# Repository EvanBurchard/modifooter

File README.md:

# Problem
Modifier keys are hard to reach. And chords involving them are
especially taxing on power users who use them frequently.

# Solution
Put it in your feet.  Like an organist, pianist or a guitarist, you
don't have to be stuck just using your hands.

# TODO:
* Rework the looping structure to use interrupts a la http://www.arduino.cc/en/Reference/AttachInterrupt

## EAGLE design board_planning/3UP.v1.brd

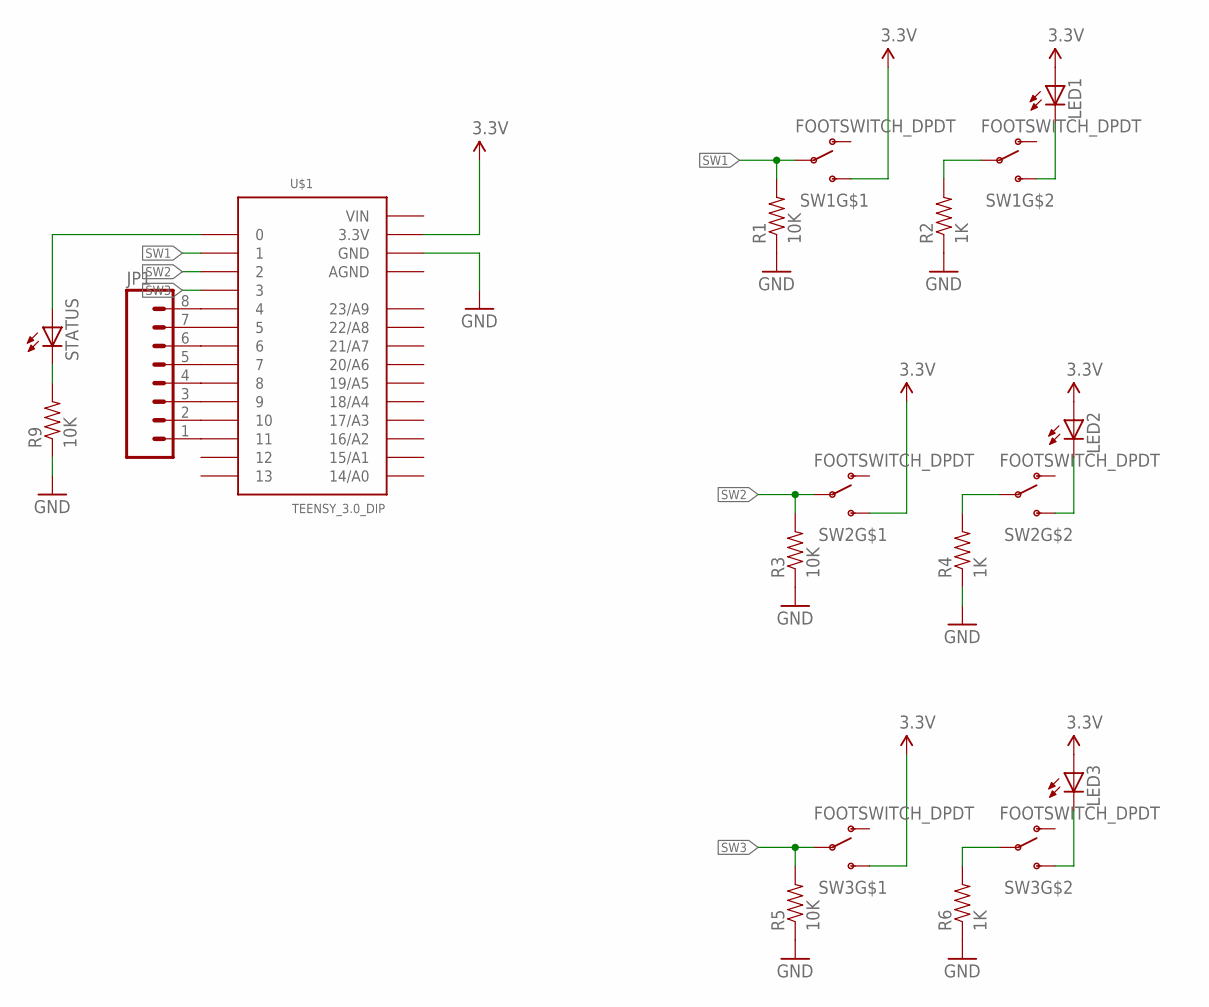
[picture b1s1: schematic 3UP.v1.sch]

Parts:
JP1: M08NO_SILK; 1X08_NO_SILK
LED1, LED2, LED3: LED5MM-W/STENCIL; LED5MM-STENCILHOLE
R1, R3, R5, R9: 10K; 0805
R2, R4, R6: 1K; 0805
STATUS: LED5MM-W/STENCIL; LED5MM-STENCILHOLE
SW1, SW2, SW3: FOOTSWITCH_DPDT; FOOTSWITCH
U$1: TEENSY_3.0_DIP

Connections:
3.3V: LED1.A, LED2.A, LED3.A, SW1.P$3 (S), SW2.P$3 (S), SW3.P$3 (S), U$1.3.3V
AGND: U$1.AGND
GND: R1.1, R2.1, R3.1, R4.1, R5.1, R6.1, R9.1, U$1.GND
unnamed: R4.2, SW2.P$5
unnamed: R2.2, SW1.P$5
unnamed: LED1.K (C), SW1.P$6 (S)
unnamed: LED2.K (C), SW2.P$6 (S)
unnamed: R6.2, SW3.P$5
unnamed: LED3.K (C), SW3.P$6 (S)
unnamed: R9.2, STATUS.K (C)
unnamed: STATUS.A, U$1.0
unnamed: JP1.1, U$1.11
unnamed: JP1.2, U$1.10
unnamed: JP1.3, U$1.9
unnamed: JP1.4, U$1.8
unnamed: JP1.5, U$1.7
unnamed: JP1.6, U$1.6
unnamed: JP1.7, U$1.5
unnamed: JP1.8, U$1.4
SW1: R1.2, SW1.P$2, U$1.1
SW2: R3.2, SW2.P$2, U$1.2
SW3: R5.2, SW3.P$2, U$1.3
VIN: U$1.VIN

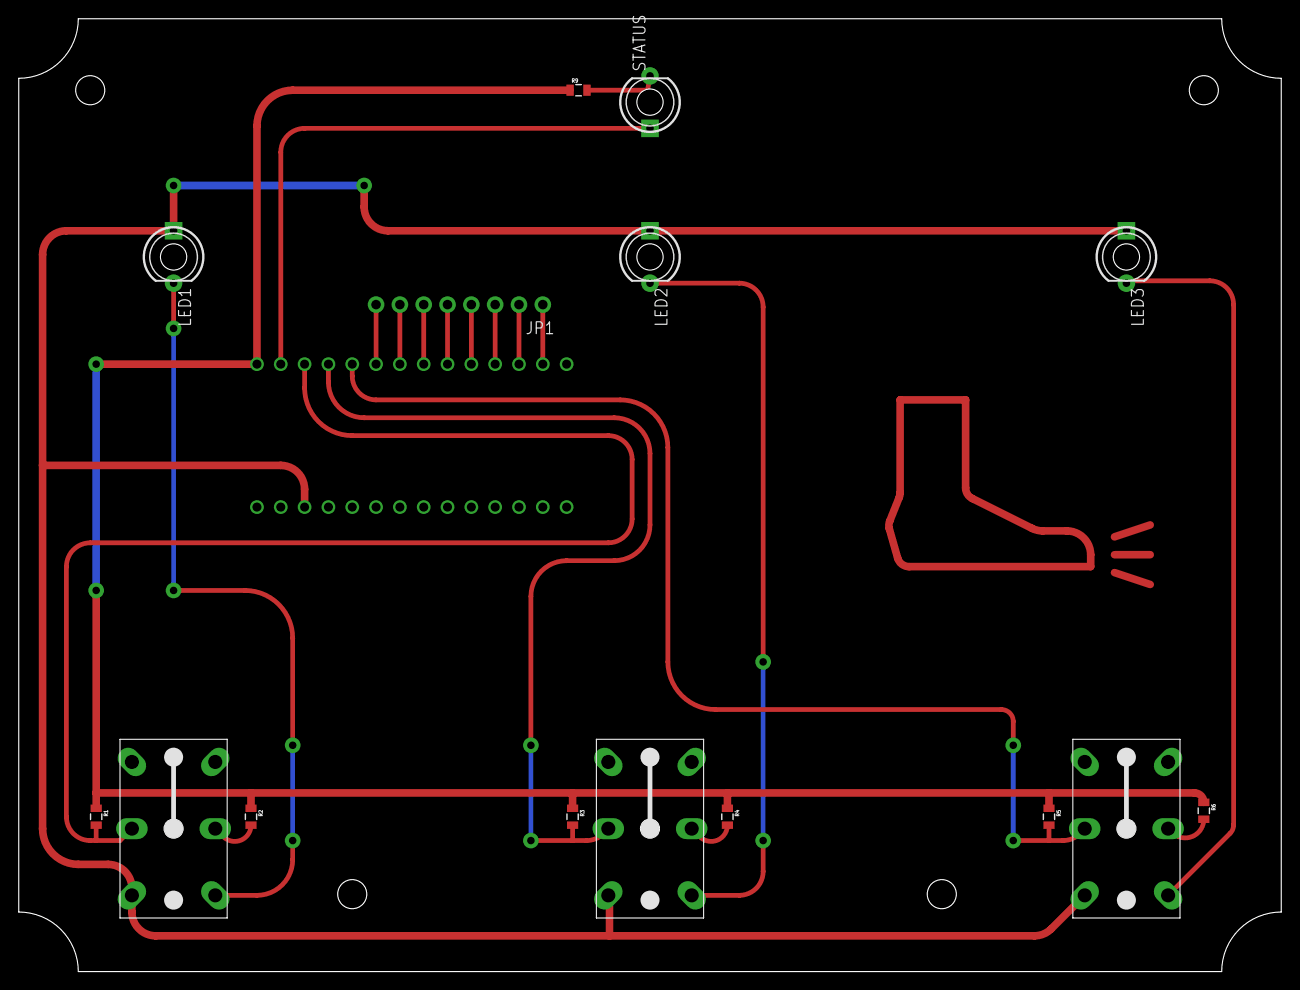
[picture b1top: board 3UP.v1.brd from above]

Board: 2 copper layers, 134.6 x 101.6 mm, 16 parts (1 on the bottom side), 21 nets.

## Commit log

2015-09-27 updated pins and keys for layout
2015-09-27 board planning files added
2015-09-28 added image
2015-09-28 readme update

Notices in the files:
parts and their libraries:
SparkFun-Passives: Licensing: Creative Commons ShareAlike 4.0 International - https://creativecommons.org/licenses/by-sa/4.0
